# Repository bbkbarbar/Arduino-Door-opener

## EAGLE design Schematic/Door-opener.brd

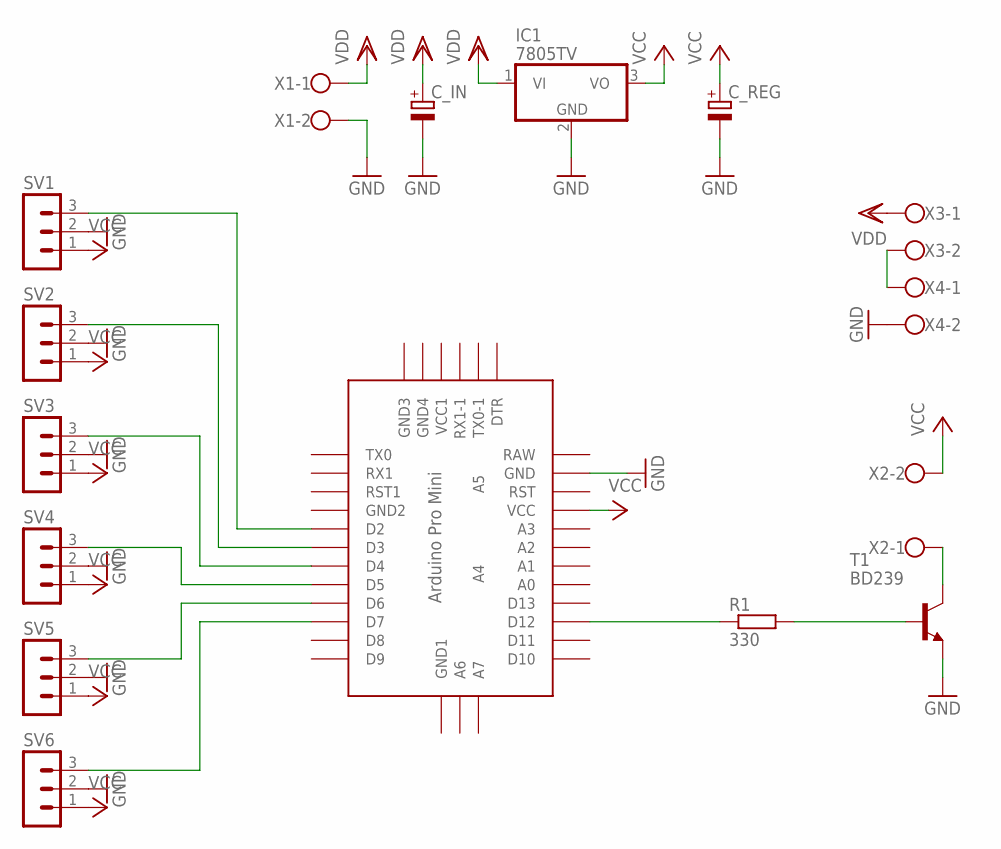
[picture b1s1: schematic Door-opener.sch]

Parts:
C_IN: CPOL-EUE3.5-8; E3,5-8
C_REG: CPOL-EUE3.5-8; E3,5-8
IC1: 7805TV; TO220V
R1: 330; 0207/10
SV1, SV2, SV3, SV4, SV5, SV6: MA03-1
T1: BD239; TO220
U$1: ABK-PRO-MINI
X1, X2, X3, X4: W237-102

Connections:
BASE: R1.1, U$1.D12
COLL: T1.2 (C), X2.1
GND: C_IN.-, C_REG.-, IC1.2 (GND), SV1.2, SV2.2, SV3.2, SV4.2, SV5.2, SV6.2, T1.3 (E), U$1.GND, X1.2, X4.2
IN1: SV1.3, U$1.D2
IN2: SV2.3, U$1.D3
IN3: SV3.3, U$1.D4
IN4: SV4.3, U$1.D5
IN5: SV5.3, U$1.D6
IN6: SV6.3, U$1.D7
unnamed: R1.2, T1.1 (B)
unnamed: X3.2, X4.1
VCC: C_REG.+, IC1.3 (VO), SV1.1, SV2.1, SV3.1, SV4.1, SV5.1, SV6.1, U$1.VCC, X2.2
VDD: C_IN.+, IC1.1 (VI), X1.1, X3.1

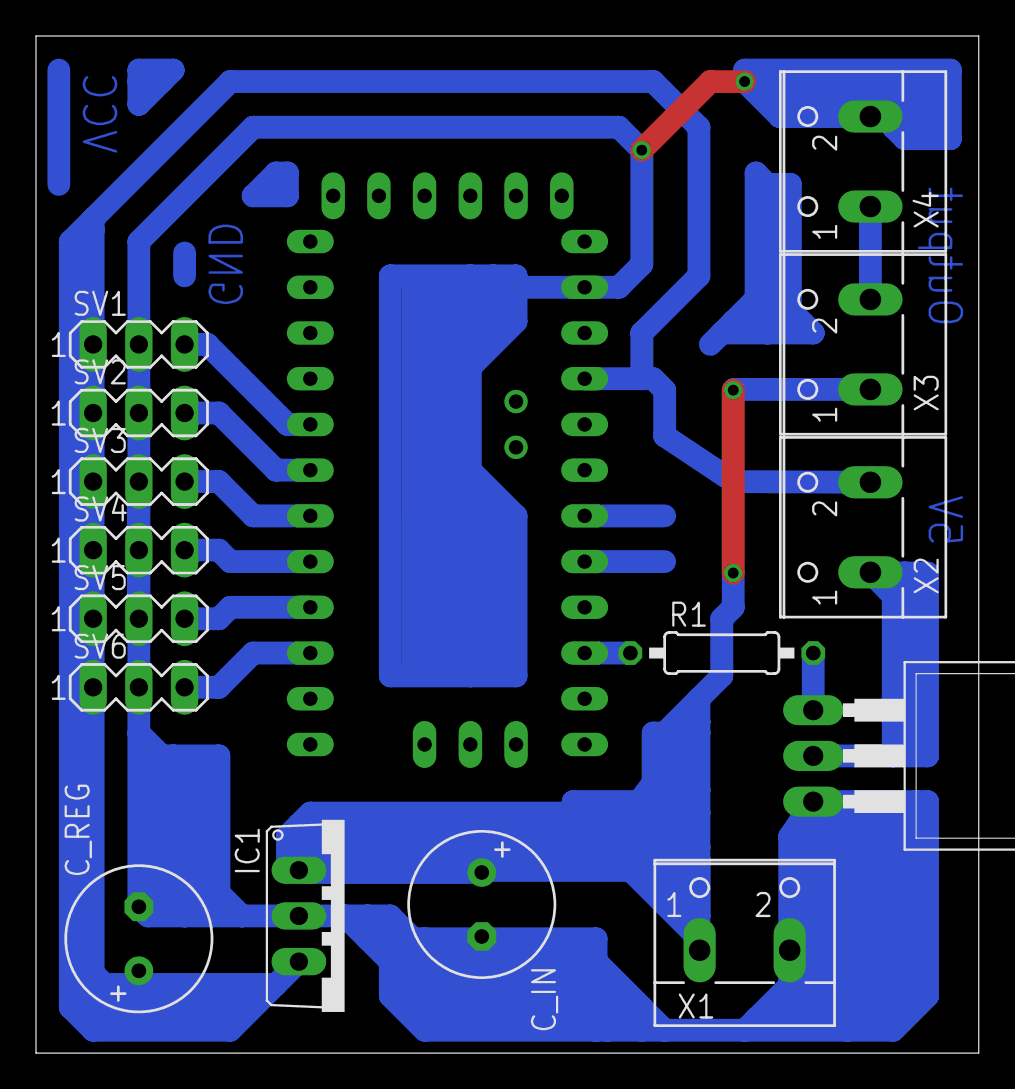
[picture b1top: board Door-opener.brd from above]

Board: 2 copper layers, 52.4 x 56.5 mm, 16 parts (0 on the bottom side), 13 nets.

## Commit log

2017-04-07 Add gitIgnore
2017-04-07 Add schematic
2017-04-07 Add printable circuite design
2017-04-07 Add parlist as orderable basket
